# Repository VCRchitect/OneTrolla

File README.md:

This is an ongoing project that aims to create a cheap, easy-to-use controller for those that have the usage of only one hand. 

The controller uses a custom circuit board that is paired with an Arduino Pro Micro and an MPU6050 Accelerometer. It has full compatibility as a wired controller for the Nintendo Switch, PC (including STEAM), Steam Deck, and Android phones (with an OTG cable or adapter).

HOW DO I USE IT?

The single analog stick on the device will act as either the left analog stick or right analog stick of a controller, depending on which mode you're in. The other stick will be controlled via motion and the accelerometer.

You can tilt the controller as if it were an arcade stick and it will act accordingly. I have inverted up and down on the left stick because, through my playtesting, it feels more natural to run forward by lifting up the controller. Not many games require running backwards, so pressing down is tilting forward, which feels less natural and, therefore, less used.

To quickly and easily swap which stick is which, press the button on the very bottom right of the controller (while you're looking directly at the buttons).

The buttons are arranged in a + pattern, just like most modern controllers. Top is X, left is Y, right is A, down is B, just like the Nintendo Switch. The two buttons below are the left trigger and right trigger.

In order to access the secondary buttons, hold down a primary button. X is Start, Y is R3, A is L3, B is Select, left trigger is LB, and right trigger is RB. If you are playing a game that requires holding a button that is considered a "primary" button, press it repeatedly and it will register as being consistently held.

To use the DPAD, press the physical analog stick in and tilt the analog stick in a direction to press the corresponding DPAD button.

The bottom left button (when you're looking directly at the buttons) is the HOME button. Tap it repeatedly to bring up the sleep menu. If you hold the HOME button until the LED changes, it will turn off the toggle function, making all the buttons function exactly the same as each other.

The toggles are for left trigger, right trigger, L3, and R3, which are buttons that are often held. Games like Zelda make this a necessity. Games like Mario 64 don't need the toggles, so they're easy to turn off.

Speaking of turning things off, it's easy to turn off the accelerometer and just use the stick for more basic games. You simply flip the physical toggle switch to the left of the B button.

If this isn't making as much sense as I'd like, review this image (some slight differences may be here because of more recent board revisions):

If that still doesn't make any sense, please check out this vide (with timestamps!) that I made to explain everything and show off some gameplay:

https://youtu.be/NdQK882Hlzc?si=iMgsrqBHt_KTq-6e

Thanks for checking out the project!

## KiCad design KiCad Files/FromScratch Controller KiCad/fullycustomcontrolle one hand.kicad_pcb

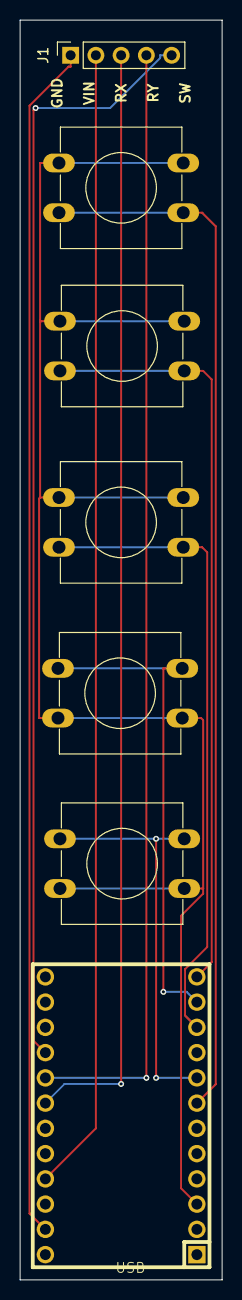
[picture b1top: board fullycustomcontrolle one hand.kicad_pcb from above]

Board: 2 copper layers, 20.3 x 126.7 mm, 7 parts (0 on the bottom side), 11 nets.

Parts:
J1: Conn_01x05_Socket; PinSocket_1x05_P2.54mm_Vertical
SW2, SW3, SW4, SW6, SW7: SW_Omron_B3FS; SW_PUSH-12mm
U1: ProMicro; ARDUINO_PRO_MICRO

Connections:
unnamed: J1.1, U1.23 (GND)
unnamed: J1.2, U1.21 (VCC)
unnamed: J1.3, U1.18 (F6)
unnamed: J1.4, U1.17 (F7)
unnamed: J1.5, U1.16 (B1)
unnamed: SW2.2, SW3.2, SW4.2, SW6.2, SW7.2, U1.3 (GND)
unnamed: SW7.1, U1.11 (B4)
unnamed: SW3.1, U1.12 (B5)
unnamed: SW4.1, U1.8 (C6)
unnamed: SW2.1, U1.7 (D4)
unnamed: SW6.1, U1.10 (E6)

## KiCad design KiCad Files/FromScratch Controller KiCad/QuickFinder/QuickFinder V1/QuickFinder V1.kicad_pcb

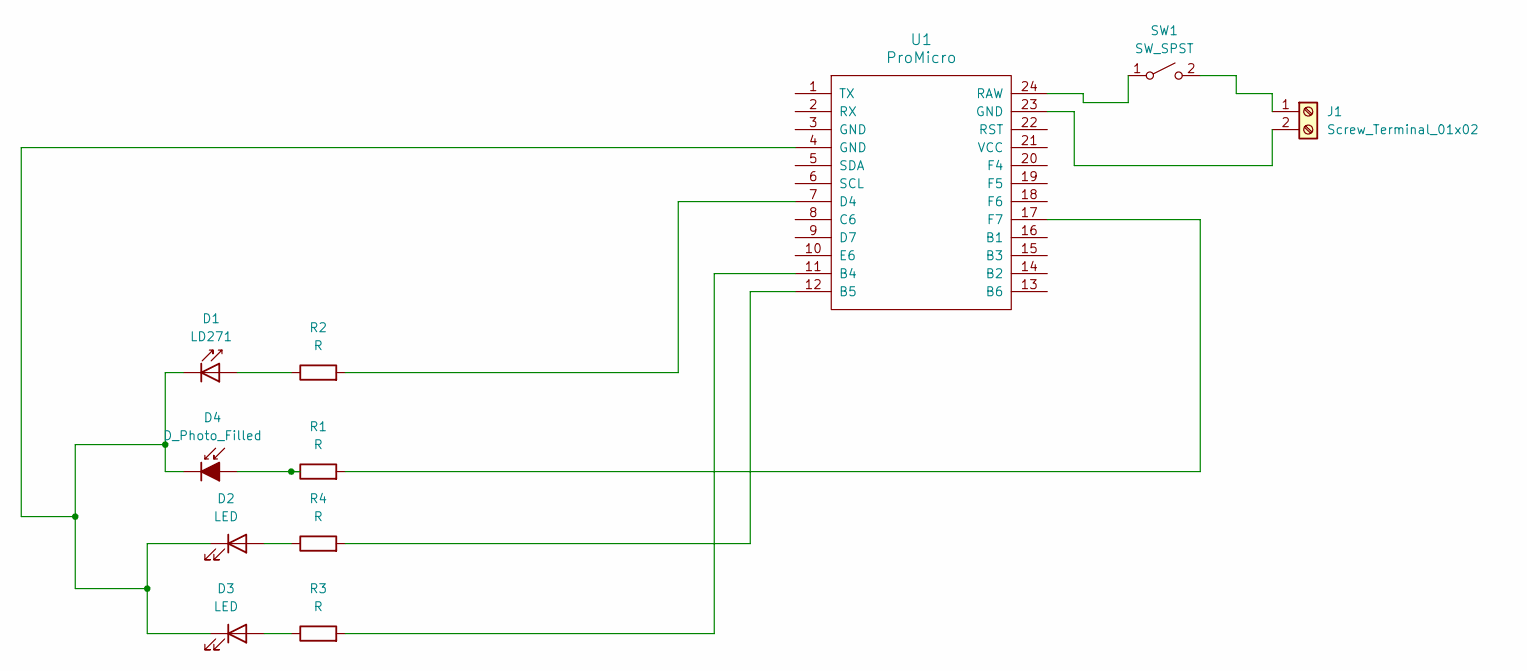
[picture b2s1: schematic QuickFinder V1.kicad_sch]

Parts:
D1: LD271; LED_D5.0mm_IRGrey
D2, D3: LED; LED_D3.0mm
D4: D_Photo_Filled; LED_D5.0mm
J1: Screw_Terminal_01x02; TerminalBlock_Phoenix_MPT-0,5-2-2.54_1x02_P2.54mm_Horizontal
R1, R2, R3, R4: R; R_Axial_DIN0207_L6.3mm_D2.5mm_P7.62mm_Horizontal
SW1: SW_SPST; SS12D00G SPDT Micro Switch
U1: ProMicro; ARDUINO_PRO_MICRO

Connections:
unnamed: D1.2 (A), R2.1
unnamed: D1.1 (K), D2.1 (K), D3.1 (K), D4.1 (K), U1.4 (GND)
unnamed: D2.2 (A), R4.1
unnamed: D3.2 (A), R3.1
unnamed: D4.2 (A), R1.1
unnamed: J1.1, SW1.2 (B)
unnamed: J1.2, U1.23 (GND)
unnamed: SW1.1 (A), U1.24 (RAW)
unnamed: R3.2, U1.11 (B4)
unnamed: R4.2, U1.12 (B5)
unnamed: R2.2, U1.7 (D4)
unnamed: R1.2, U1.17 (F7)

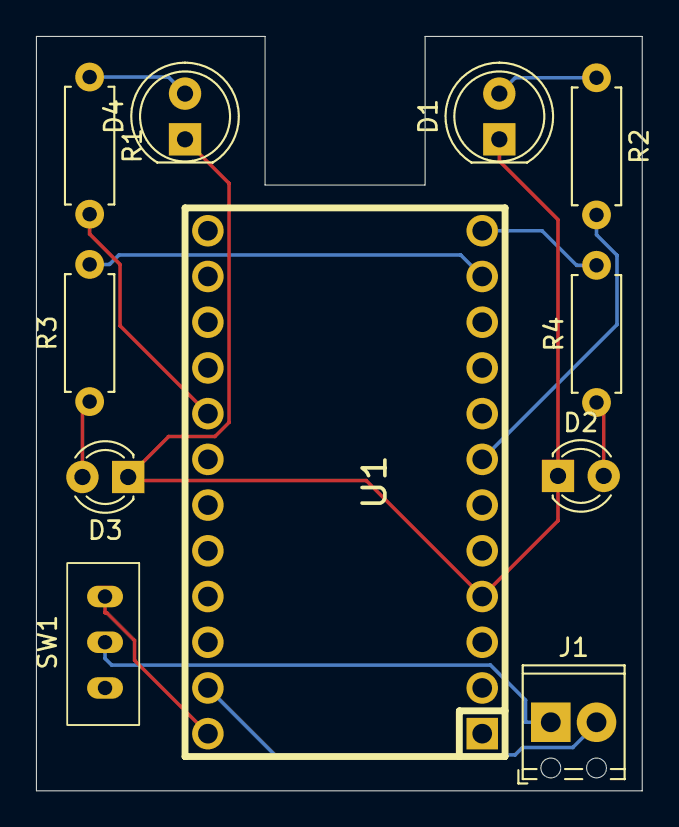
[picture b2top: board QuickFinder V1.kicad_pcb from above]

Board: 2 copper layers, 33.7 x 41.9 mm, 11 parts (0 on the bottom side), 12 nets.

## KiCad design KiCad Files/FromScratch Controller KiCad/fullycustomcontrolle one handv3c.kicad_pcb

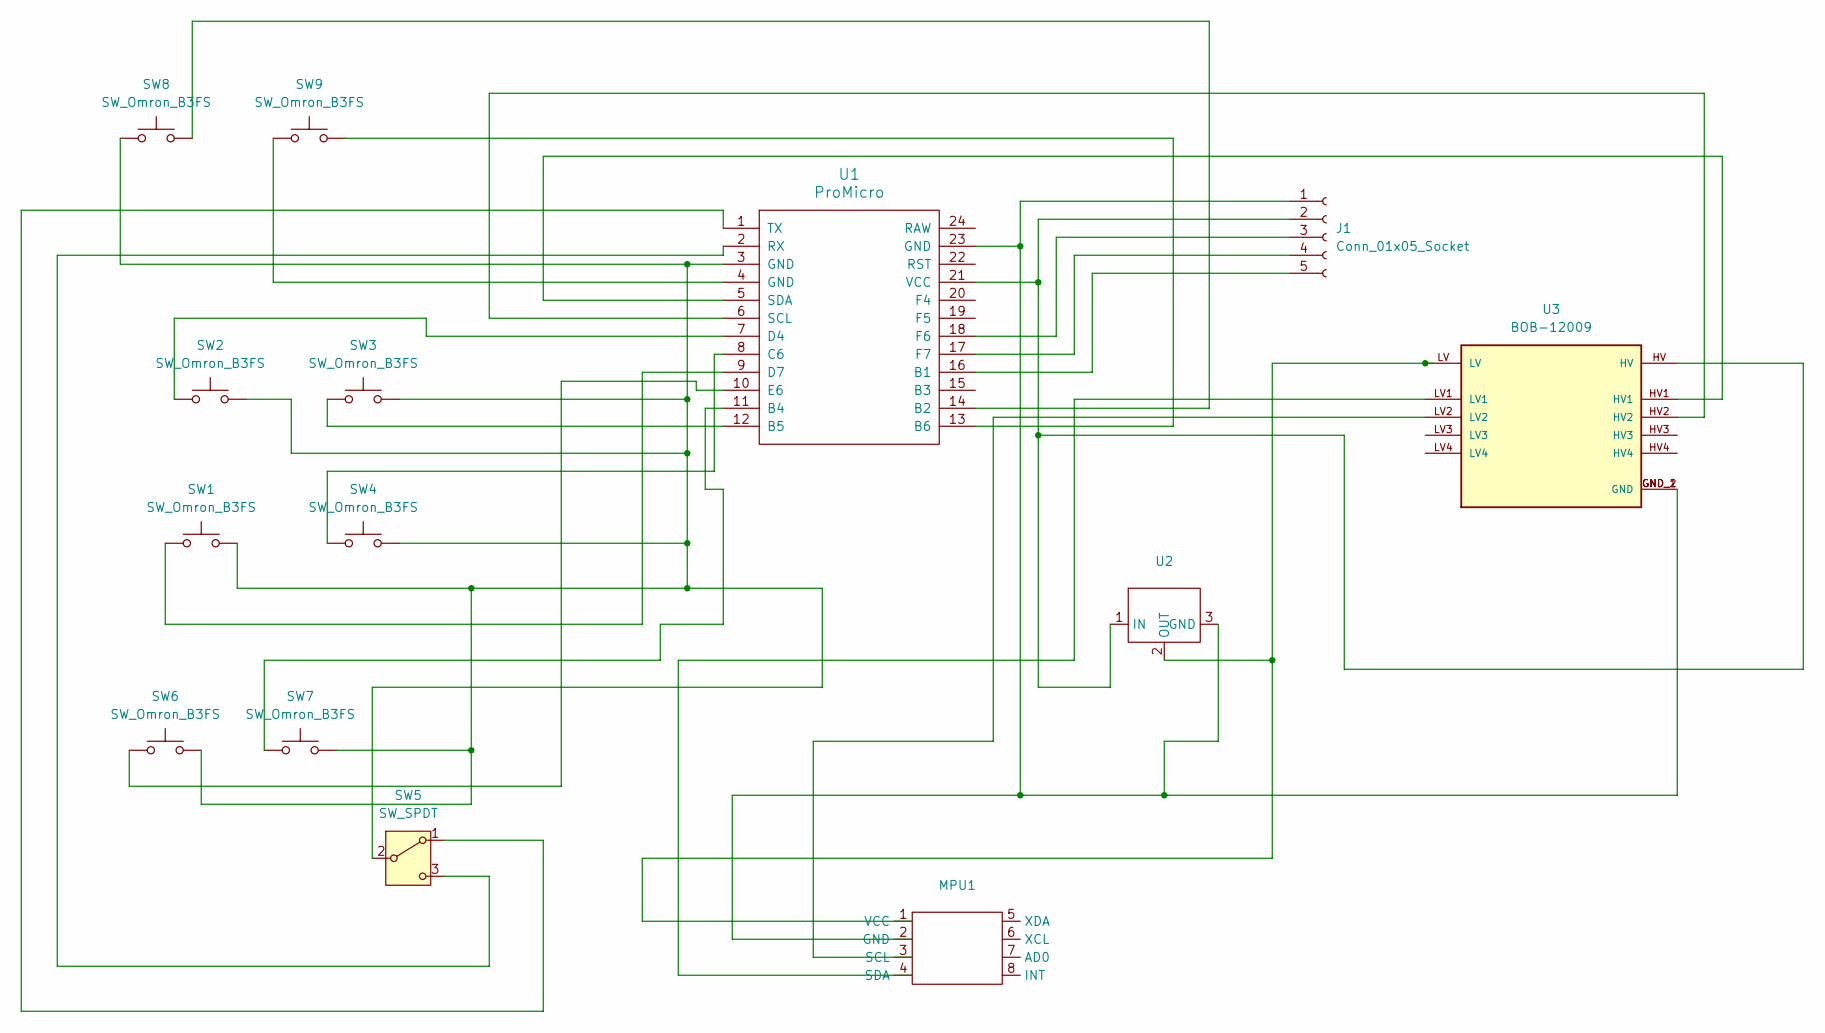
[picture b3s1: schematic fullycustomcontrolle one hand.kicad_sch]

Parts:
J1: Conn_01x05_Socket; PinSocket_1x05_P2.54mm_Vertical
MPU1: MPU6050 Accelerometer
SW1, SW2, SW3, SW4, SW6, SW7, SW8, SW9: SW_Omron_B3FS; SW_PUSH-12mm
SW5: SW_SPDT; SS12D00G SPDT Micro Switch
U1: ProMicro; ARDUINO_PRO_MICRO
U2: 3.3v InOutGnd Voltage Regulator
U3: BOB-12009; CONV_BOB-12009; PARTREV 01

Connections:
unnamed: J1.1, MPU1.2 (GND), U1.23 (GND), U2.3 (GND), U3.GND_1 (GND), U3.GND_2 (GND)
unnamed: J1.2, U1.21 (VCC), U2.1 (IN), U3.HV
unnamed: J1.3, U1.18 (F6)
unnamed: J1.4, U1.17 (F7)
unnamed: J1.5, U1.16 (B1)
unnamed: MPU1.3 (SCL), U3.LV2
unnamed: MPU1.4 (SDA), U3.LV1
unnamed: MPU1.1 (VCC), U2.2 (OUT), U3.LV
unnamed: SW5.1 (A), U1.1 (TX)
unnamed: SW1.2, SW2.2, SW3.2, SW4.2, SW5.2 (B), SW6.2, SW7.2, SW8.1, U1.3 (GND)
unnamed: SW5.3 (C), U1.2 (RX)
unnamed: SW9.1, U1.4 (GND)
unnamed: SW8.2, U1.14 (B2)
unnamed: SW7.1, U1.11 (B4)
unnamed: SW3.1, U1.12 (B5)
unnamed: SW9.2, U1.13 (B6)
unnamed: SW4.1, U1.8 (C6)
unnamed: SW2.1, U1.7 (D4)
unnamed: SW1.1, U1.9 (D7)
unnamed: SW6.1, U1.10 (E6)
unnamed: U1.6 (SCL), U3.HV2
unnamed: U1.5 (SDA), U3.HV1

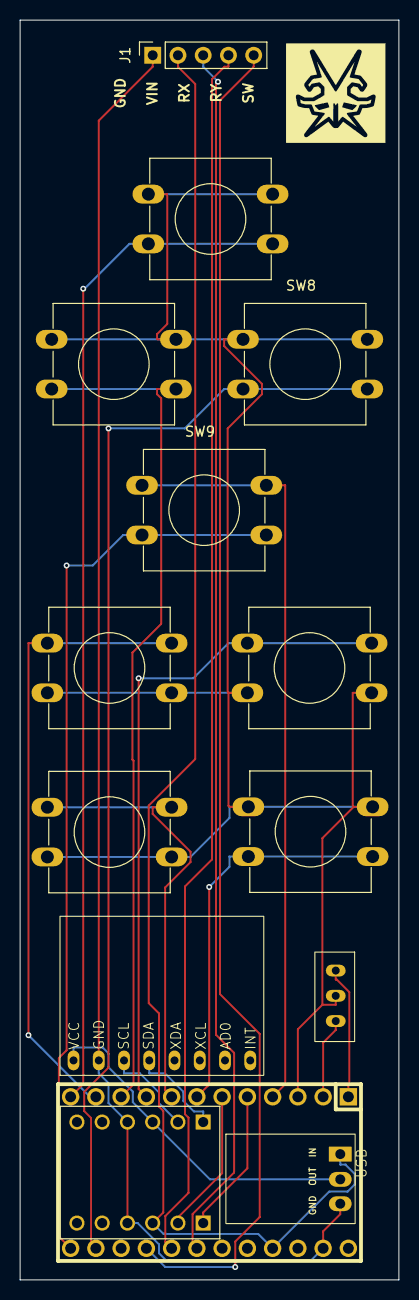
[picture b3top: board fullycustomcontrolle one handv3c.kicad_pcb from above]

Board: 2 copper layers, 38.1 x 126.7 mm, 14 parts (0 on the bottom side), 22 nets.

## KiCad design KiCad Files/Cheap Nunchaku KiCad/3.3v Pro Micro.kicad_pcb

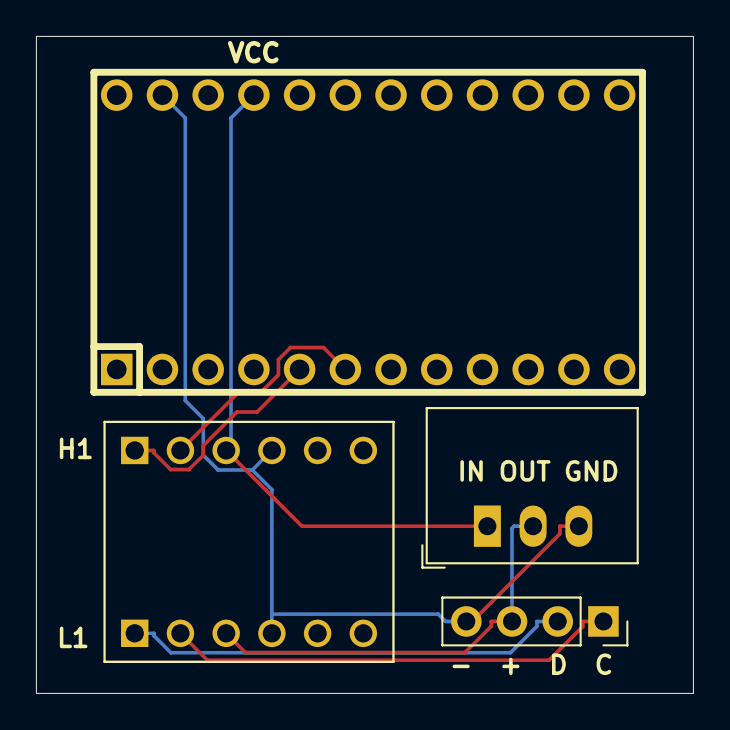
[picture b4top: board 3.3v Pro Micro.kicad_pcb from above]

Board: 2 copper layers, 36.5 x 36.5 mm, 4 parts (0 on the bottom side), 7 nets.

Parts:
J1: Conn_01x04_Socket; PinSocket_1x04_P2.54mm_Vertical
U2: ProMicro; ARDUINO_PRO_MICRO
U3: BOB-12009; CONV_BOB-12009
U4: Converter_DCDC_RECOM_R-78E-0.5_THT

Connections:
unnamed: J1.1, U3.LV2
unnamed: J1.2, U3.LV1
unnamed: J1.3, U3.LV, U4.2 (OUT)
unnamed: J1.4, U2.23 (GND), U3.GND_1 (GND), U3.GND_2 (GND), U4.3 (GND)
unnamed: U2.6 (SCL), U3.HV2
unnamed: U2.5 (SDA), U3.HV1
unnamed: U2.21 (VCC), U3.HV, U4.1 (IN)

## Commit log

2024-07-15 Initial Commit and Beginnings
2024-07-15 Tweaked
2024-07-16 KBM Addition
2024-07-17 Added Main PCB w Wii Connector
2024-07-17 Almost Forgot KiCad
2024-07-17 Restructured files and new script
2024-07-25 NS coding done completely?
2024-07-27 Mini Boss edit
2024-08-12 SUPER FINAL VERSION GOOD
2024-09-17 Controller Revision 2
2024-09-19 Updates with 3D Models
2024-09-27 Now with casing!
2024-09-27 Updated case files to be more ergonomic
2024-09-27 Opened Up Toggle Switch
2024-09-29 New Control Scheme
2025-02-24 Some updates to the layout
    I'm starting on board revision 3 so that I can add a couple more features and requested quality of life items.
2025-03-08 Updated the PCB files for V3
    WIll explain the layout in the next commit
2025-03-13 Front Plate Done
    3D Print File Done for V4!
2025-03-14 Update OneTrollaV4 Back Plate.stl
    Fixed the dimensions of the backplate!
